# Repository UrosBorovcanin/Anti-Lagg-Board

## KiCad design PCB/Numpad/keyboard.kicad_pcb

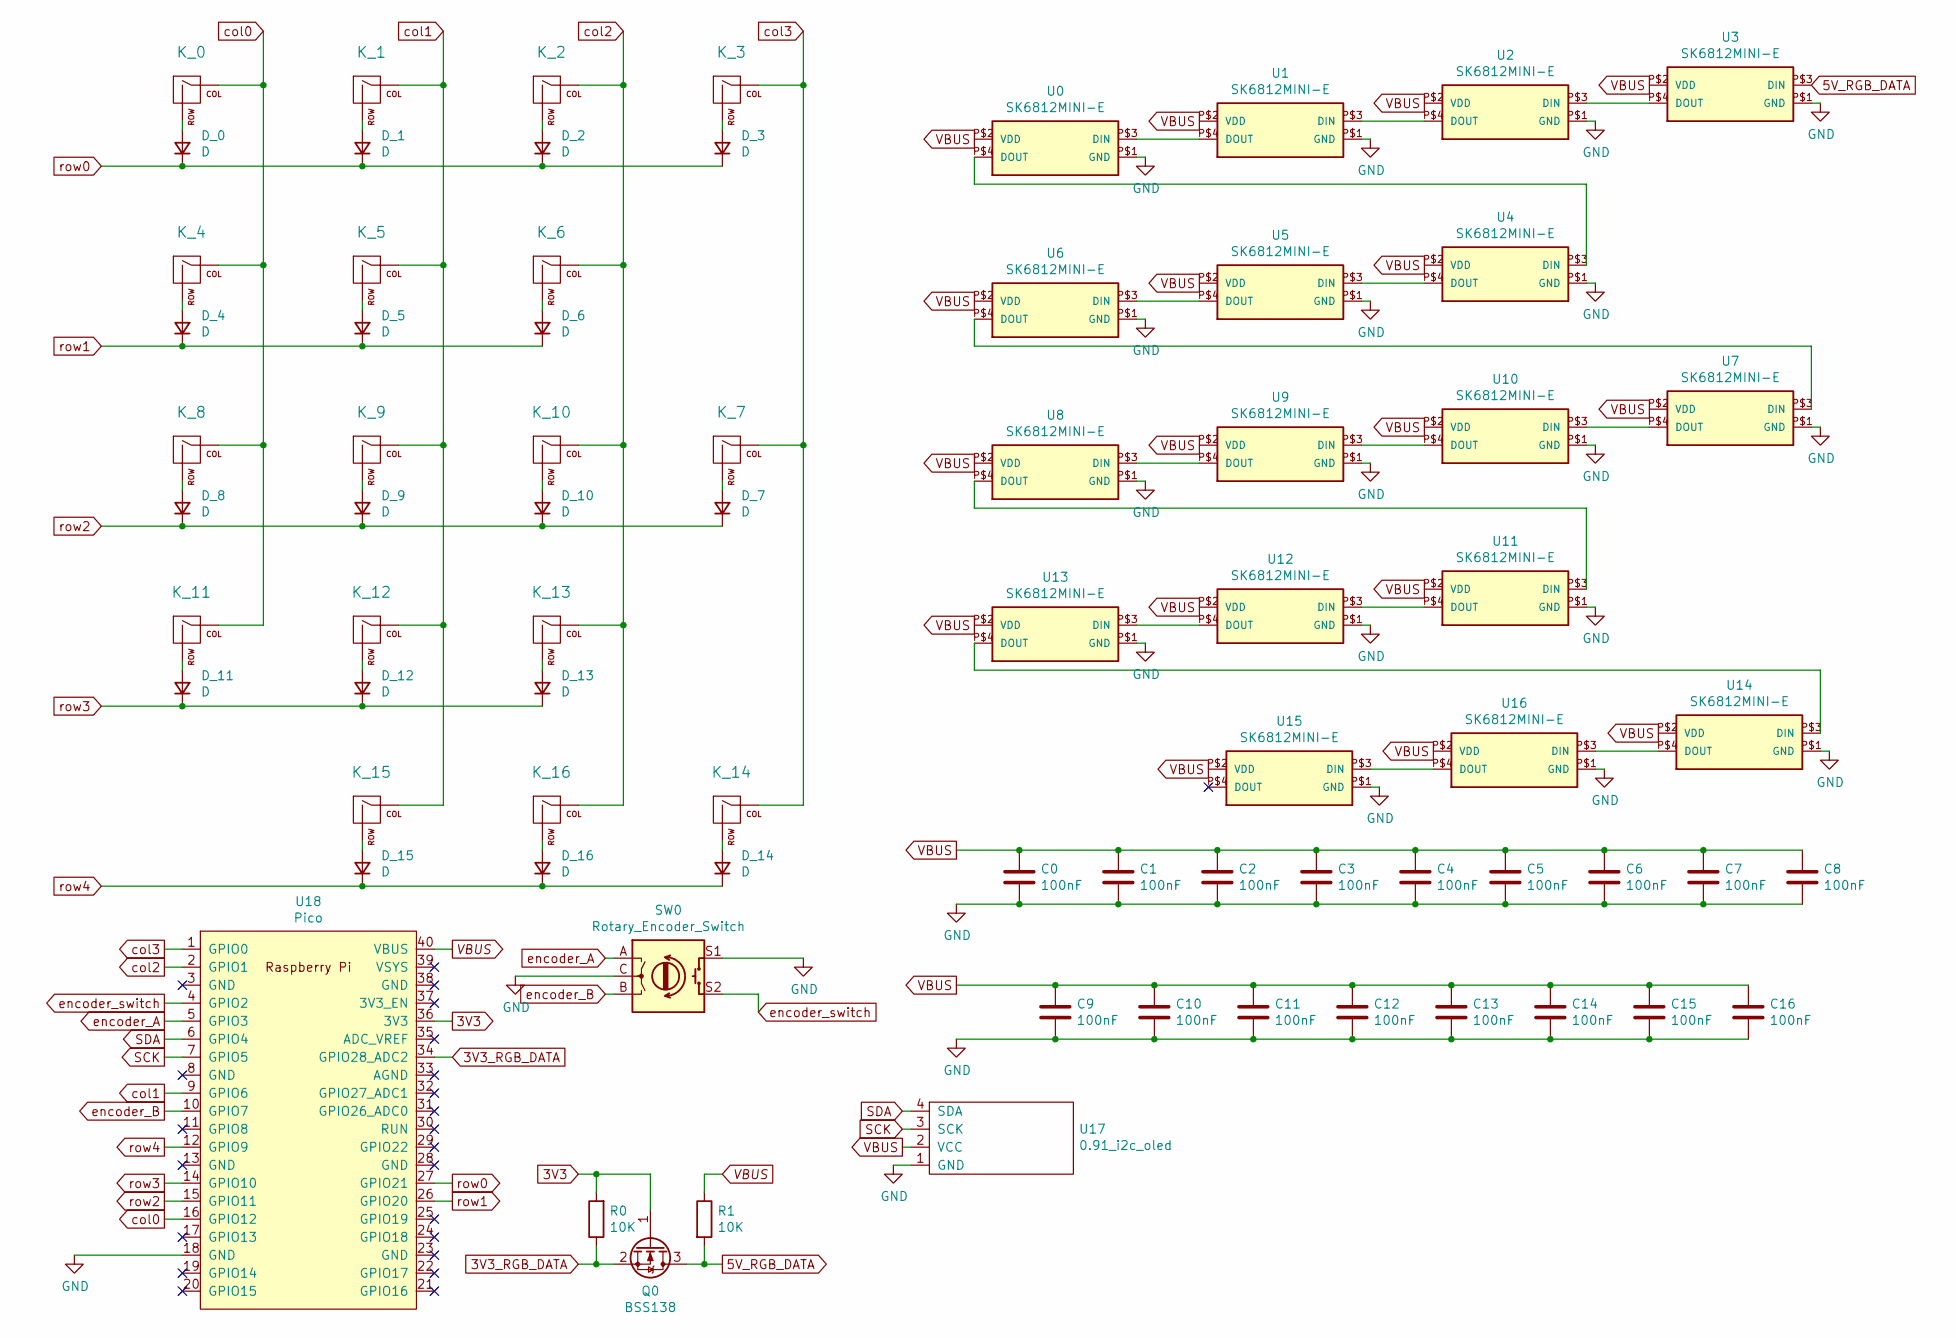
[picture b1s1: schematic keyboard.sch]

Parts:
C0, C1, C2, C3, C4, C5, C6, C7, C8, C9, C10, C11, C12, C13, C14, C15, C16: 100nF; C_0603_1608Metric_Pad1.08x0.95mm_HandSolder
D_0, D_1, D_2, D_3, D_4, D_5, D_6, D_7, D_8, D_9, D_10, D_11, D_12, D_13, D_14, D_15, D_16: D; D_0603_1608Metric_Pad1.05x0.95mm_HandSolder
K_0, K_1, K_2, K_3, K_4, K_5, K_6, K_8, K_9, K_10, K_11, K_12, K_13, K_16: KEYSW; MXOnly-1U-NoLED
K_7, K_14, K_15: KEYSW; MXOnly-2U-NoLED
Q0: BSS138; SOT-23
R0, R1: 10K; R_0603_1608Metric_Pad0.98x0.95mm_HandSolder
SW0: Rotary_Encoder_Switch; RotaryEncoder_Alps_EC11E-Switch_Vertical_H20mm
U0, U1, U2, U3, U4, U5, U6, U7, U8, U9, U10, U11, U12, U13, U14, U15, U16: SK6812MINI-E; SK6812MINI-E_RVRSMOUNT
U17: 0.91_i2c_oled
U18: Pico; RPi_Pico_TH_no_DEBUG_no_pads

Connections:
3V3: Q0.1 (G), R0.2, U18.36 (3V3)
3V3_RGB_DATA: Q0.2 (S), R0.1, U18.34 (GPIO28_ADC2)
5V_RGB_DATA: Q0.3 (D), R1.2, U3.P$3 (DIN)
GND: C0.2, C1.2, C2.2, C3.2, C4.2, C5.2, C6.2, C7.2, C8.2, C9.2, C10.2, C11.2, C12.2, C13.2, C14.2, C15.2, C16.2, SW0.C, SW0.S1, U0.P$1 (GND), U1.P$1 (GND), U2.P$1 (GND), U3.P$1 (GND), U4.P$1 (GND), U5.P$1 (GND), U6.P$1 (GND), U7.P$1 (GND), U8.P$1 (GND), U9.P$1 (GND), U10.P$1 (GND), U11.P$1 (GND), U12.P$1 (GND), U13.P$1 (GND), U14.P$1 (GND), U15.P$1 (GND), U16.P$1 (GND), U17.1 (GND), U18.18 (GND)
unnamed: D_0.2 (A), K_0.2 (ROW)
unnamed: D_1.2 (A), K_1.2 (ROW)
unnamed: D_2.2 (A), K_2.2 (ROW)
unnamed: D_3.2 (A), K_3.2 (ROW)
unnamed: D_4.2 (A), K_4.2 (ROW)
unnamed: D_5.2 (A), K_5.2 (ROW)
unnamed: D_6.2 (A), K_6.2 (ROW)
unnamed: D_7.2 (A), K_7.2 (ROW)
unnamed: D_8.2 (A), K_8.2 (ROW)
unnamed: D_9.2 (A), K_9.2 (ROW)
unnamed: D_10.2 (A), K_10.2 (ROW)
unnamed: D_11.2 (A), K_11.2 (ROW)
unnamed: D_12.2 (A), K_12.2 (ROW)
unnamed: D_13.2 (A), K_13.2 (ROW)
unnamed: D_14.2 (A), K_14.2 (ROW)
unnamed: D_15.2 (A), K_15.2 (ROW)
unnamed: D_16.2 (A), K_16.2 (ROW)
unnamed: U0.P$3 (DIN), U1.P$4 (DOUT)
unnamed: U0.P$4 (DOUT), U4.P$3 (DIN)
unnamed: U1.P$3 (DIN), U2.P$4 (DOUT)
unnamed: U2.P$3 (DIN), U3.P$4 (DOUT)
unnamed: U4.P$4 (DOUT), U5.P$3 (DIN)
unnamed: U5.P$4 (DOUT), U6.P$3 (DIN)
unnamed: U6.P$4 (DOUT), U7.P$3 (DIN)
unnamed: U8.P$3 (DIN), U9.P$4 (DOUT)
unnamed: U7.P$4 (DOUT), U10.P$3 (DIN)
unnamed: U9.P$3 (DIN), U10.P$4 (DOUT)
unnamed: U8.P$4 (DOUT), U11.P$3 (DIN)
unnamed: U11.P$4 (DOUT), U12.P$3 (DIN)
unnamed: U12.P$4 (DOUT), U13.P$3 (DIN)
unnamed: U13.P$4 (DOUT), U14.P$3 (DIN)
unnamed: U14.P$4 (DOUT), U16.P$3 (DIN)
unnamed: U15.P$3 (DIN), U16.P$4 (DOUT)
SCK: U17.3 (SCK), U18.7 (GPIO5)
SDA: U17.4 (SDA), U18.6 (GPIO4)
VBUS: C0.1, C1.1, C2.1, C3.1, C4.1, C5.1, C6.1, C7.1, C8.1, C9.1, C10.1, C11.1, C12.1, C13.1, C14.1, C15.1, C16.1, R1.1, U0.P$2 (VDD), U1.P$2 (VDD), U2.P$2 (VDD), U3.P$2 (VDD), U4.P$2 (VDD), U5.P$2 (VDD), U6.P$2 (VDD), U7.P$2 (VDD), U8.P$2 (VDD), U9.P$2 (VDD), U10.P$2 (VDD), U11.P$2 (VDD), U12.P$2 (VDD), U13.P$2 (VDD), U14.P$2 (VDD), U15.P$2 (VDD), U16.P$2 (VDD), U17.2 (VCC), U18.40 (VBUS)
col0: K_0.1 (COL), K_4.1 (COL), K_8.1 (COL), K_11.1 (COL), U18.16 (GPIO12)
col1: K_1.1 (COL), K_5.1 (COL), K_9.1 (COL), K_12.1 (COL), K_15.1 (COL), U18.9 (GPIO6)
col2: K_2.1 (COL), K_6.1 (COL), K_10.1 (COL), K_13.1 (COL), K_16.1 (COL), U18.2 (GPIO1)
col3: K_3.1 (COL), K_7.1 (COL), K_14.1 (COL), U18.1 (GPIO0)
encoder_A: SW0.A, U18.5 (GPIO3)
encoder_B: SW0.B, U18.10 (GPIO7)
encoder_switch: SW0.S2, U18.4 (GPIO2)
row0: D_0.1 (K), D_1.1 (K), D_2.1 (K), D_3.1 (K), U18.27 (GPIO21)
row1: D_4.1 (K), D_5.1 (K), D_6.1 (K), U18.26 (GPIO20)
row2: D_7.1 (K), D_8.1 (K), D_9.1 (K), D_10.1 (K), U18.15 (GPIO11)
row3: D_11.1 (K), D_12.1 (K), D_13.1 (K), U18.14 (GPIO10)
row4: D_14.1 (K), D_15.1 (K), D_16.1 (K), U18.12 (GPIO9)

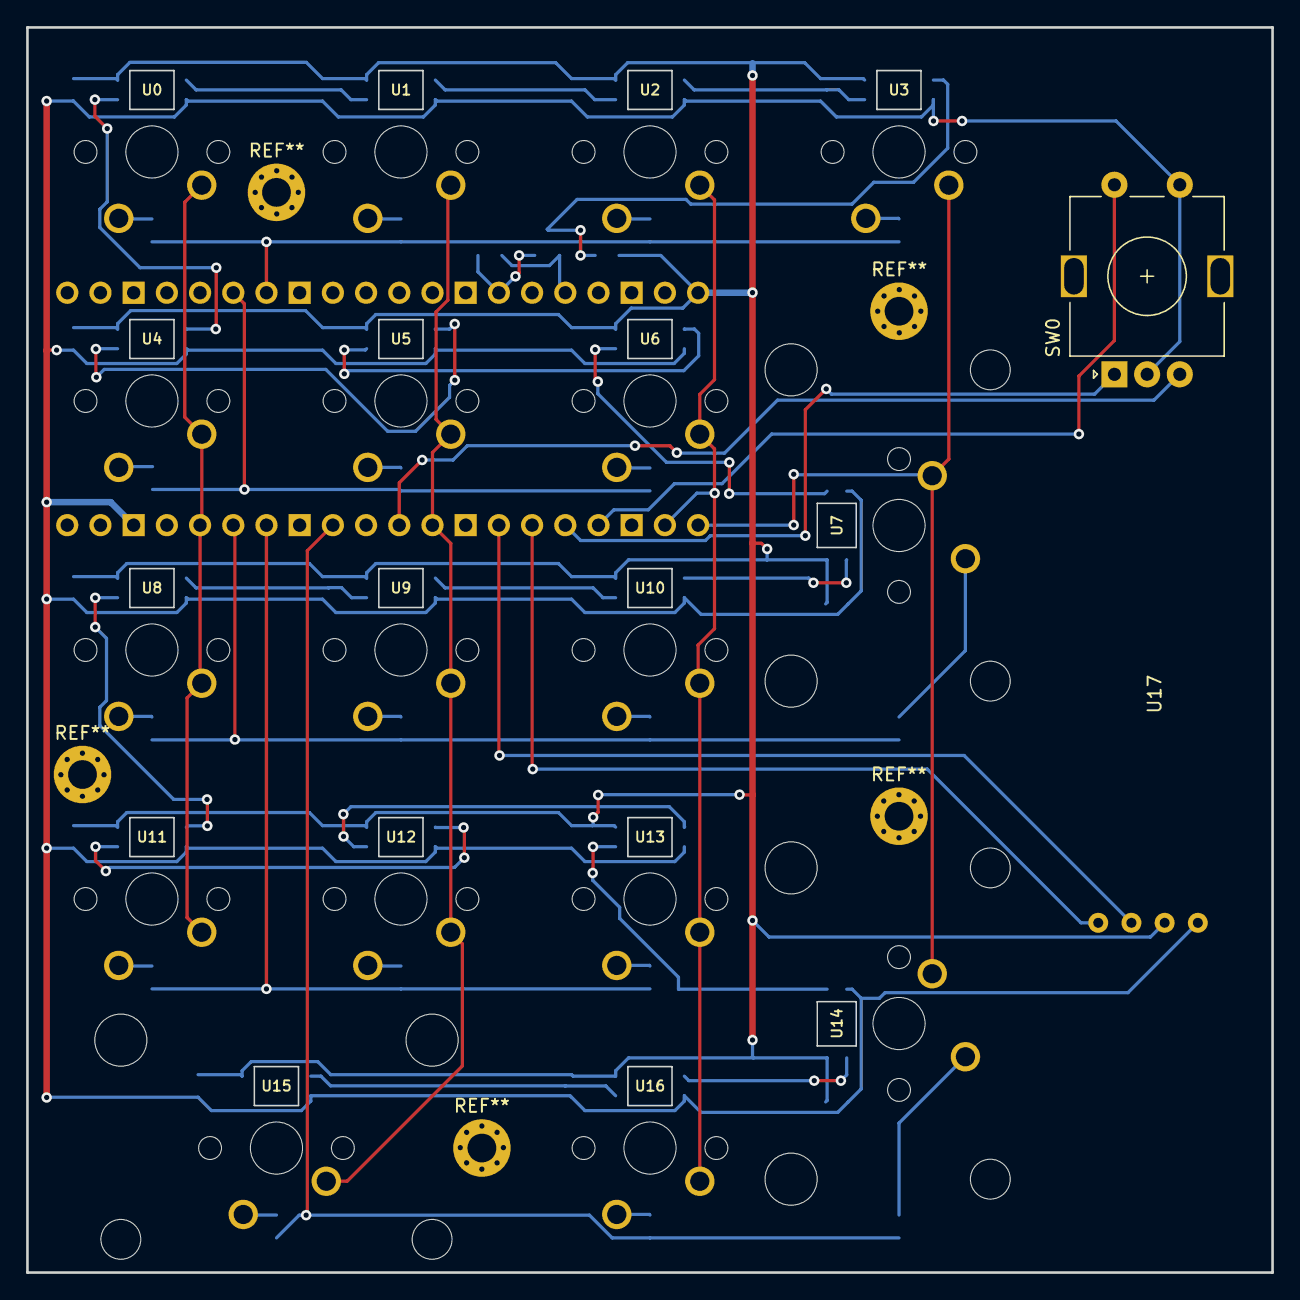
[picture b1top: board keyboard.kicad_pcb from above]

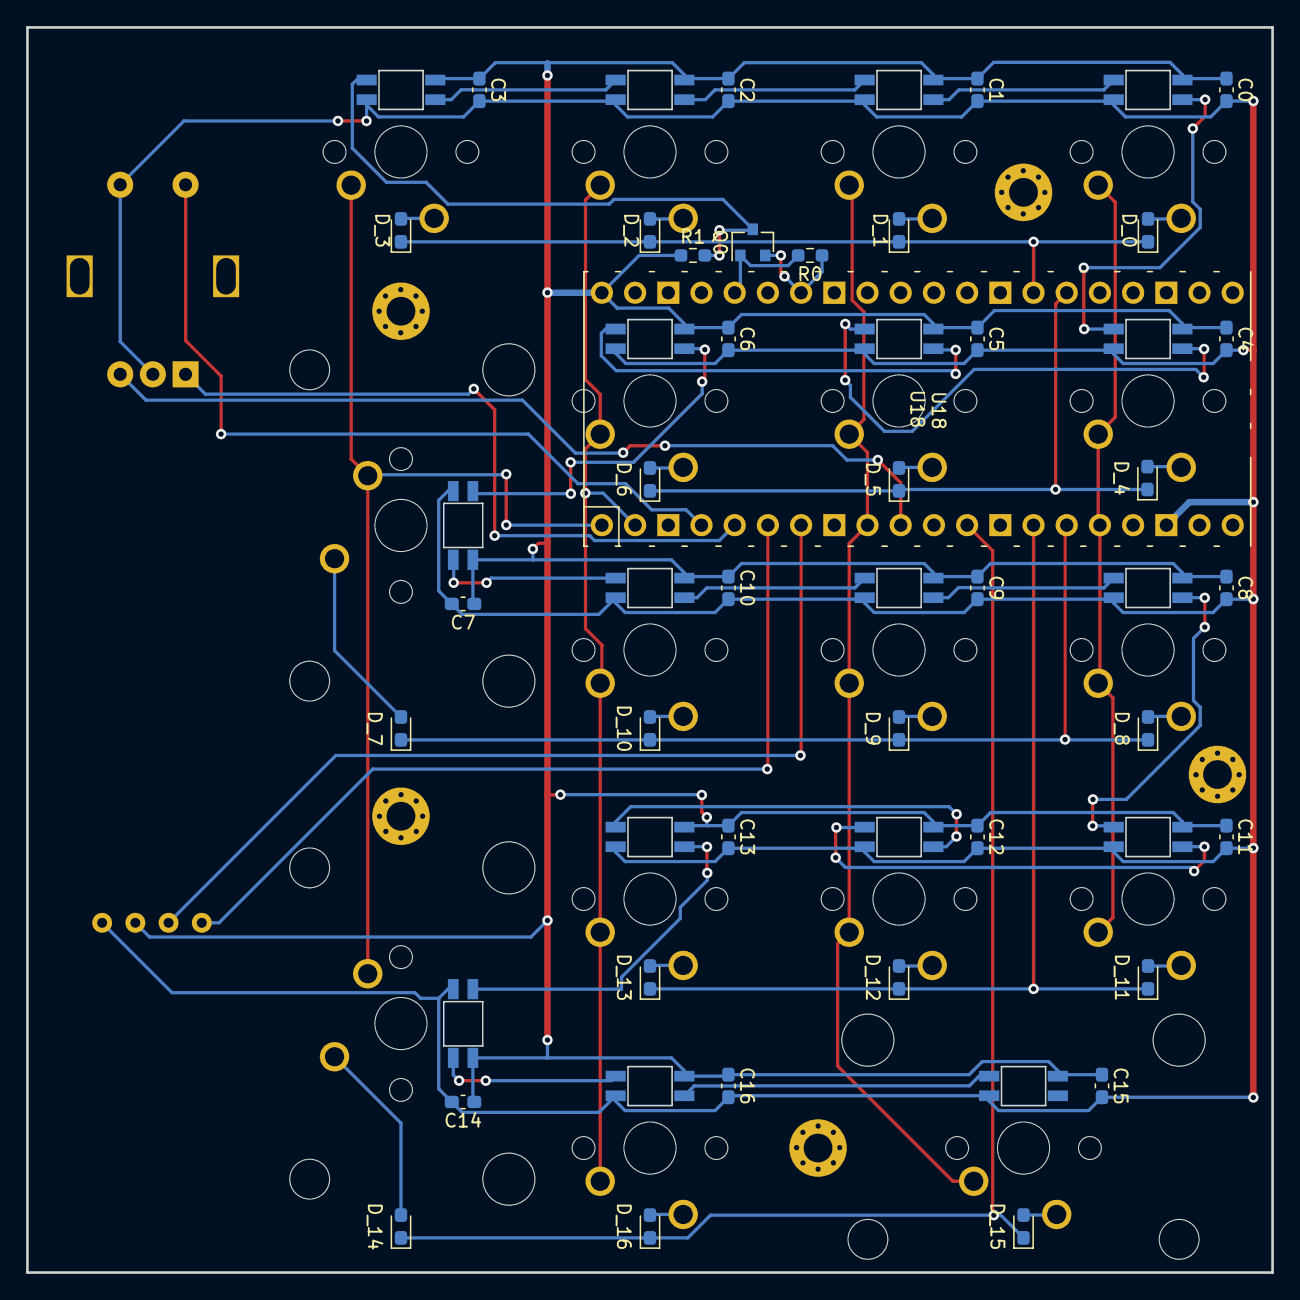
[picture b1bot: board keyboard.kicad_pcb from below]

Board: 2 copper layers, 95.3 x 95.2 mm, 74 parts (38 on the bottom side), 52 nets.

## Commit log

2022-06-07 Improved the folder structure
2022-06-10 Added files necessary for scanning and mapping the keyboard
2022-06-12 Implemented the detect_keypresses function
2022-07-06 Added debounce logic and simplified certain pieces of code
2022-07-07 Added basic comments, missing hid keycodes and test mapping
2022-07-07 Simplified NKRO keyboard reports
2022-07-13 Modified setup functions and started debugging the keybaord module
2022-08-04 Debug version of the firmware works, release does not
2022-11-08 Numpad V0.1 PCB prototype
2022-11-08 Fixed a compilation bug, cleaned up some code
2022-12-13 mapped the keys for the first Numpad prototype
2022-12-13 Added a Numpad plate prototype
2022-12-19 Added and oled screen test and multithreading(needs fixing)
2022-12-19 Added encoder code, multicore still needs fixing
2022-12-19 Updated the Core1 main, multicore still not functional
2022-12-20 Added screen update testing function(needs debugging)
2022-12-20 Added a simpler encoder interrupt method with debouncing
2023-01-03 Found the source of the freezing issue in usbd.c lines 532, 533
2023-01-03 Solved the oled freezing issue
2023-03-14 Encoder code redone using a state machine
